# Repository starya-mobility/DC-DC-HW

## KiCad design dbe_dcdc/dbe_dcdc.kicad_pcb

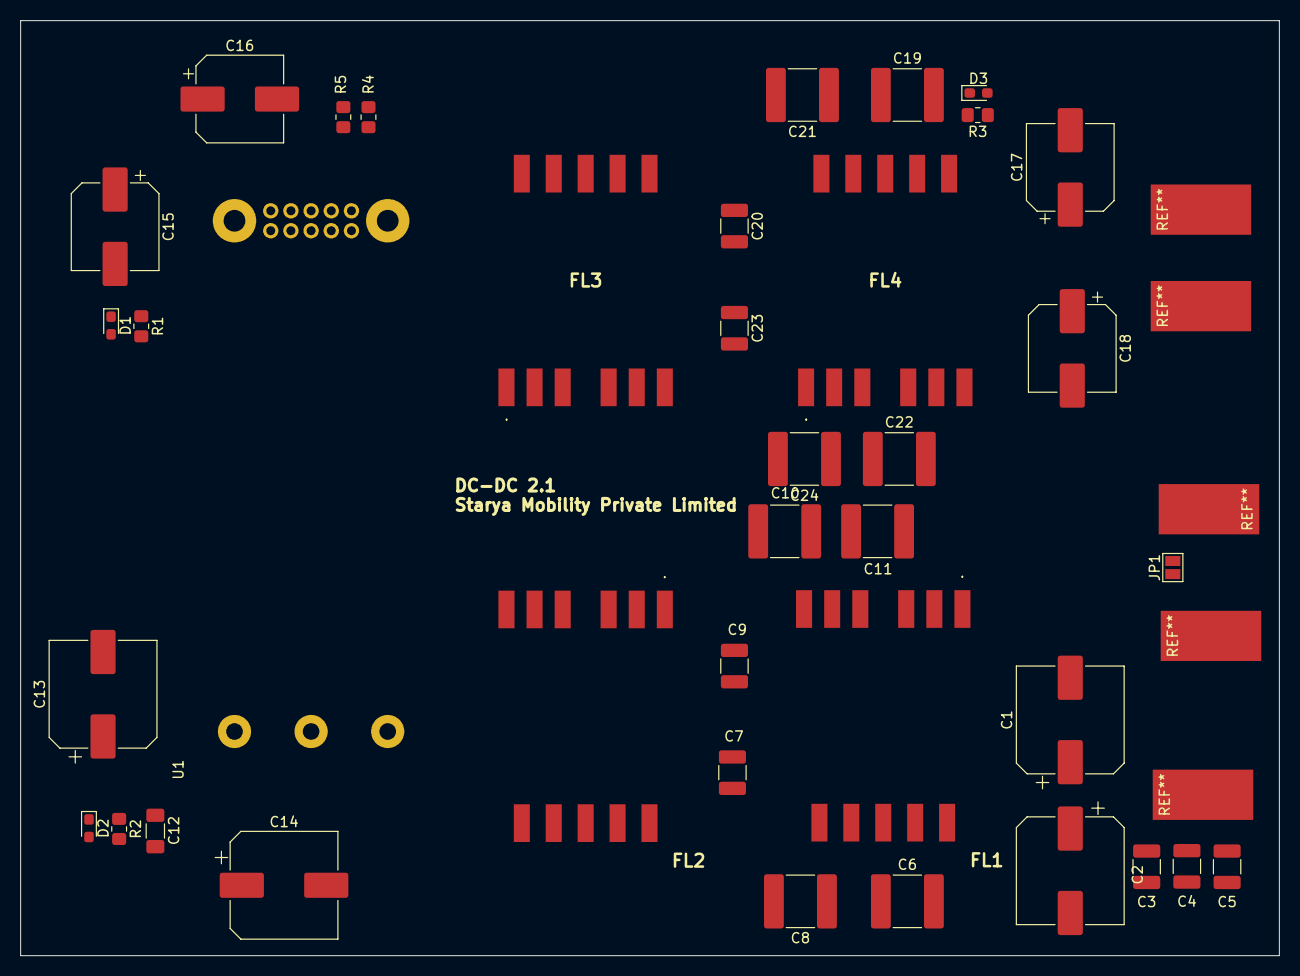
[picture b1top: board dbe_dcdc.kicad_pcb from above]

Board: 4 copper layers, 125.2 x 93.0 mm, 38 parts (0 on the bottom side), 16 nets, no tracks yet.

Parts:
C1: 865080453014; CP_Elec_10x10.5
C2, C13, C14: 865060857005; CP_Elec_10x10.5
C3, C4, C5, C7, C9, C20, C23: GRM32ER72A105KA01L; C_1210_3225Metric_Pad1.33x2.70mm_HandSolder
C6, C8, C10, C11, C19, C21, C22, C24: GRM55DR72J224KW01L; C_2220_5650Metric_Pad1.97x5.40mm_HandSolder
C12: GRM319R72A104KA01D; C_1206_3216Metric_Pad1.33x1.80mm_HandSolder
C15, C16, C17, C18: 865080453014; CP_Elec_8x10.5
D1: Amber; LED_0603_1608Metric_Pad1.05x0.95mm_HandSolder
D2: Red; LED_0603_1608Metric_Pad1.05x0.95mm_HandSolder
D3: Green; LED_0603_1608Metric_Pad1.05x0.95mm_HandSolder
FL1, FL2, FL3, FL4: PH9407.504NLT; PH9407_504NLT
JP1: On/OFF; SolderJumper-2_P1.3mm_Open_Pad1.0x1.5mm
R1: 220; R_0805_2012Metric_Pad1.20x1.40mm_HandSolder
R2: 20k; R_0805_2012Metric_Pad1.20x1.40mm_HandSolder
R3: 2k; R_0805_2012Metric_Pad1.20x1.40mm_HandSolder
R4, R5: 47k; R_0805_2012Metric_Pad1.20x1.40mm_HandSolder
U1: DBE0125V2NBC

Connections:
+12V: C17.1, C18.1, FL4.7 (N2_1), FL4.8 (N2_2), R3.2
+VDC: C1.1, C2.1, C3.1, C4.1, C5.1, FL1.10 (N2_3), FL1.11 (N2_4)
-VDC: C1.2, C2.2, C3.2, C4.2, C5.2, C6.2, C8.2, C10.2, C11.2, C17.2, C18.2, C19.2, C21.2, C22.2, C24.2, FL1.2 (N1_1), FL1.3 (N1_2), FL4.5 (N1_3), FL4.6 (N1_4)
-VIN: C12.2, C13.2, C14.2, C15.2, C16.2, D1.1 (K), D2.1 (K), D3.1 (K), FL2.5 (N1_3), FL2.6 (N1_4), FL3.2 (N1_1), FL3.3 (N1_2), JP1.1 (A), R4.2, R5.2, U1.4 (-VIN), U1.5 (-VOUT), U1.7 (-S), U1.13 (DGND)
unnamed: C6.1, C7.1, C8.1, C9.1, FL1.7 (N2_1), FL1.8 (N2_2), FL2.10 (N2_3), FL2.11 (N2_4)
unnamed: C7.2, C9.2, C10.1, C11.1, FL1.5 (N1_3), FL1.6 (N1_4), FL2.2 (N1_1), FL2.3 (N1_2)
unnamed: C15.1, C16.1, FL3.10 (N2_3), FL3.11 (N2_4), U1.6 (+S), U1.16 (+VOUT)
unnamed: D1.2 (A), R1.2
unnamed: D2.2 (A), R2.2
unnamed: D3.2 (A), R3.1
unnamed: C19.1, C20.1, C21.1, C23.1, FL3.7 (N2_1), FL3.8 (N2_2), FL4.10 (N2_3), FL4.11 (N2_4)
unnamed: R4.1, U1.8 (SA0)
unnamed: R5.1, U1.9 (SA1)
P_GOOD: R1.1, U1.12 (PG)
VIN: C12.1, C13.1, C14.1, FL2.7 (N2_1), FL2.8 (N2_2), R2.1, U1.1 (+VIN)
~EN: JP1.2 (B), U1.2 (RC)

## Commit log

2023-03-30 non EMC compliant Design
2023-03-31 layout and schema changes for out and in filtering
